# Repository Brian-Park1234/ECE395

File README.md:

Hello!

This is Brian Park (Brianp7) github for all ECE395 Files.

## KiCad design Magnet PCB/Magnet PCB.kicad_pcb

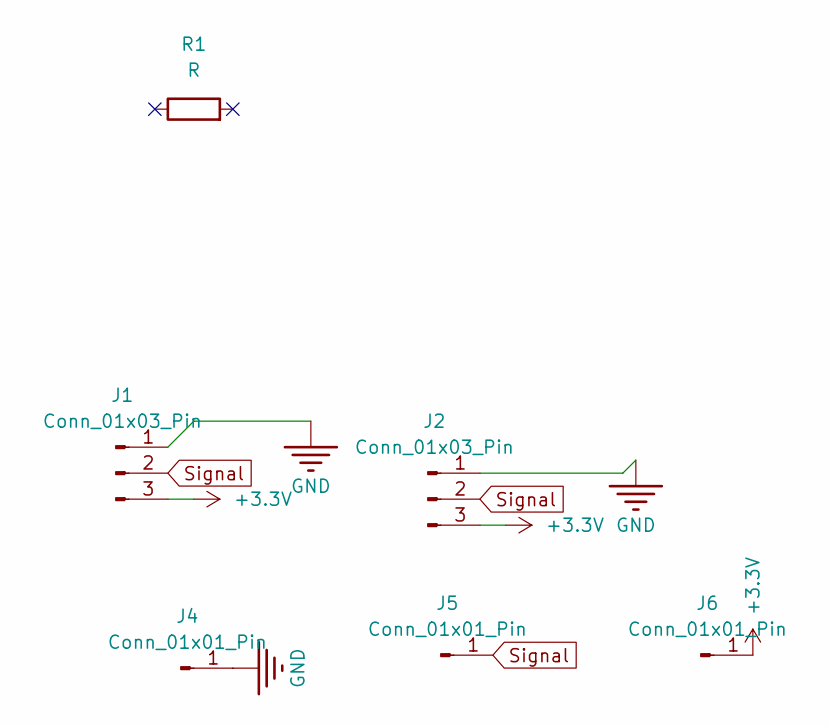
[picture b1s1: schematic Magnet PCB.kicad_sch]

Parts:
J1, J2: Conn_01x03_Pin; JST_SH_SM03B-SRSS-TB_1x03-1MP_P1.00mm_Horizontal
J4, J5, J6: Conn_01x01_Pin; CONN_0900-2-15-20-75-14-11-0_MIM
R1: R; R_0815_2038Metric

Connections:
+3.3V: J1.3, J2.3, J6.1
GND: J1.1, J2.1, J4.1
Signal: J1.2, J2.2, J5.1

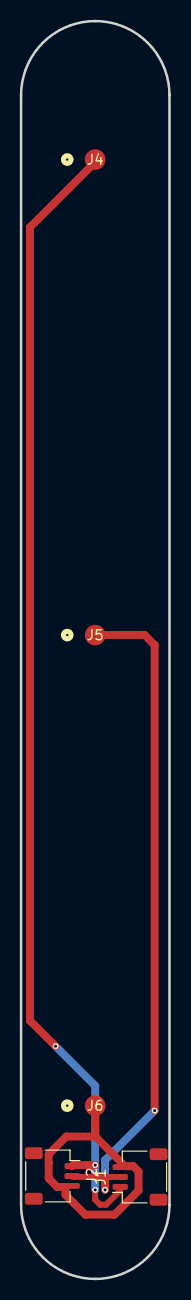
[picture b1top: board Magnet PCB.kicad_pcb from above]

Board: 2 copper layers, 15.0 x 127.0 mm, 6 parts (1 on the bottom side), 3 nets.

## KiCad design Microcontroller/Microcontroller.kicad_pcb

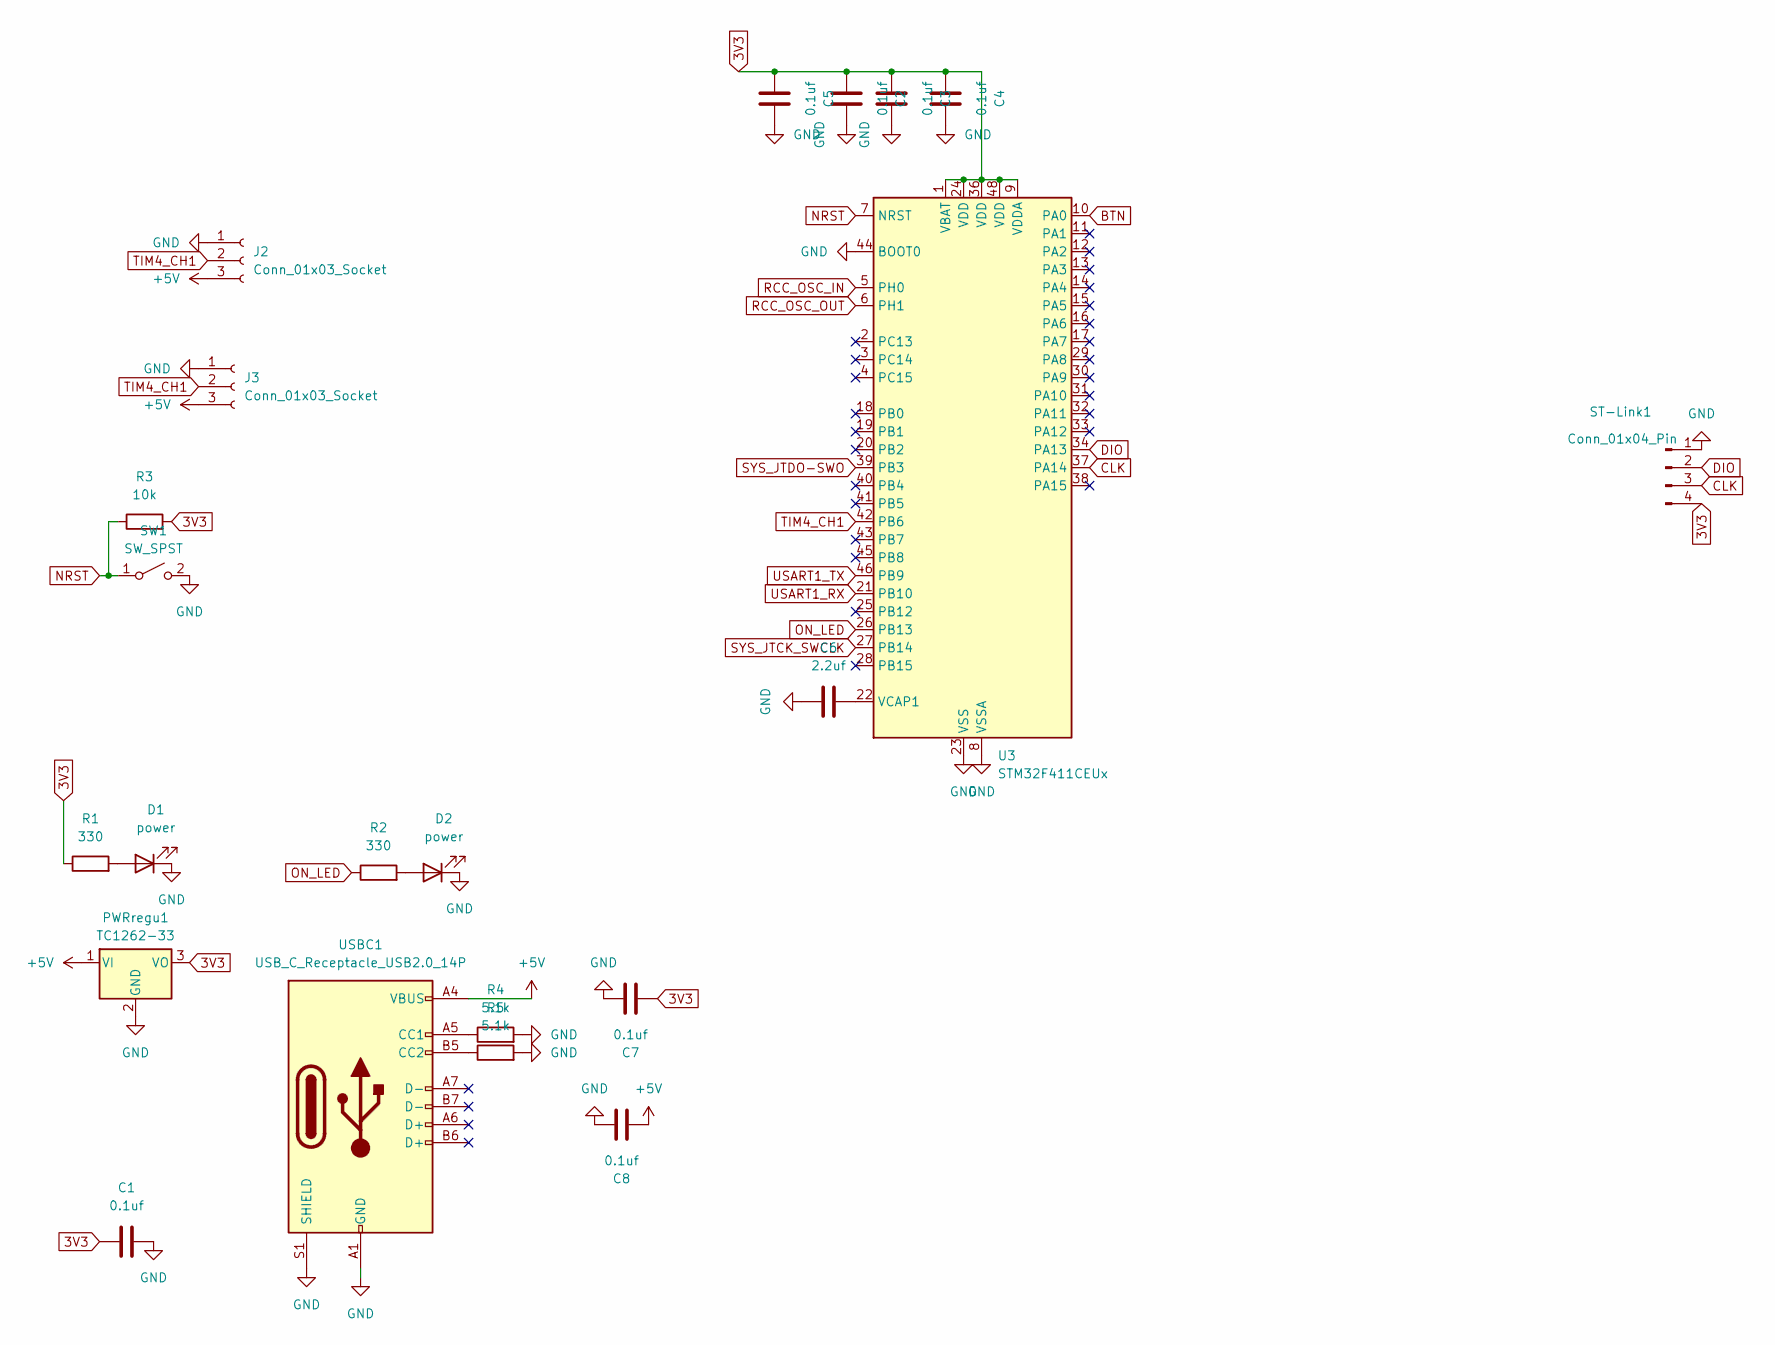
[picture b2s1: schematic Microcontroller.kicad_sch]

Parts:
C1, C2, C3, C4, C5, C7, C8: 0.1uf; C_0805_2012Metric_Pad1.18x1.45mm_HandSolder
C6: 2.2uf; C_0805_2012Metric_Pad1.18x1.45mm_HandSolder
D1, D2: power; D_0805_2012Metric
J2, J3: Conn_01x03_Socket; JST_SH_SM03B-SRSS-TB_1x03-1MP_P1.00mm_Horizontal
PWRregu1: TC1262-33; SOT-223-3_TabPin2
R1, R2: 330; R_0805_2012Metric
R3: 10k; R_0805_2012Metric
R4, R5: 5.1k; R_0805_2012Metric
ST-Link1: Conn_01x04_Pin; PinHeader_1x04_P2.54mm_Vertical
SW1: SW_SPST; SW_PUSH_6mm
U3: STM32F411CEUx; QFN-48-1EP_7x7mm_P0.5mm_EP5.6x5.6mm
USBC1: USB_C_Receptacle_USB2.0_14P; USB_C_Receptacle_GCT_USB4085

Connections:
3V3: C1.1, C2.1, C3.1, C4.1, C5.1, C7.1, PWRregu1.3 (VO), R1.1, R3.2, ST-Link1.4, U3.1 (VBAT), U3.9 (VDDA), U3.24 (VDD), U3.36 (VDD), U3.48 (VDD)
+5V: C8.1, J2.3, J3.3, PWRregu1.1 (VI), USBC1.A4 (VBUS), USBC1.A9 (VBUS), USBC1.B4 (VBUS), USBC1.B9 (VBUS)
BTN: U3.10 (PA0)
CLK: ST-Link1.3, U3.37 (PA14)
DIO: ST-Link1.2, U3.34 (PA13)
GND: C1.2, C2.2, C3.2, C4.2, C5.2, C6.2, C7.2, C8.2, D1.1 (K), D2.1 (K), J2.1, J3.1, PWRregu1.2 (GND), R4.2, R5.2, ST-Link1.1, SW1.2 (B), U3.8 (VSSA), U3.23 (VSS), U3.35 (VSS), U3.44 (BOOT0), U3.47 (VSS), U3.49 (VSS), USBC1.A1 (GND), USBC1.A12 (GND), USBC1.B1 (GND), USBC1.B12 (GND), USBC1.S1 (SHIELD); also elsewhere on the board
NRST: R3.1, SW1.1 (A), U3.7 (NRST)
unnamed: D1.2 (A), R1.2
unnamed: D2.2 (A), R2.2
unnamed: C6.1, U3.22 (VCAP1)
unnamed 10: R4.1, USBC1.A5 (CC1); also elsewhere on the board
unnamed: R5.1, USBC1.B5 (CC2)
ON_LED: R2.1, U3.26 (PB13)
RCC_OSC_IN: U3.5 (PH0)
RCC_OSC_OUT: U3.6 (PH1)
SYS_JTCK_SWCLK: U3.27 (PB14)
SYS_JTDO-SWO: U3.39 (PB3)
TIM4_CH1: J2.2, J3.2, U3.42 (PB6)
USART1_RX: U3.21 (PB10)
USART1_TX: U3.46 (PB9)

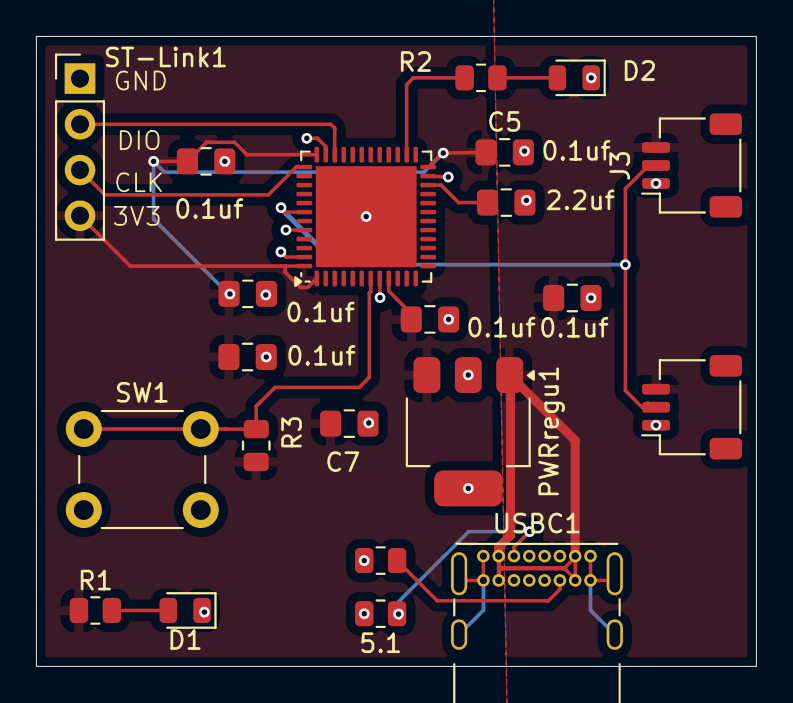
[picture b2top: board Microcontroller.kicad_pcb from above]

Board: 2 copper layers, 40.0 x 35.0 mm, 22 parts (0 on the bottom side), 13 nets.

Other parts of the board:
5.1: 5.1k; R_0805_2012Metric

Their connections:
GND: 5.1.2; also elsewhere on the board
unnamed 10: 5.1.1; also elsewhere on the board

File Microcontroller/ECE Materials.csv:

Reference,Value,Datasheet,Footprint,Qty,DNP
"C1,C2,C3,C4,C5,C6,C7,C8",0.1uf,~,Capacitor_SMD:C_0805_2012Metric_Pad1.18x1.45mm_HandSolder,8,
"D1,D2",power,~,Diode_SMD:D_0805_2012Metric,2,
"J2,J3",Conn_01x03_Socket,~,Connector_JST:JST_SH_SM03B-SRSS-TB_1x03-1MP_P1.00mm_Horizontal,2,
PWRregu1,TC1262-33,http://ww1.microchip.com/downloads/en/DeviceDoc/21373C.pdf,Package_TO_SOT_SMD:SOT-223-3_TabPin2,1,
"R1,R2",330,~,Resistor_SMD:R_0805_2012Metric,2,
R3,10k,~,Resistor_SMD:R_0805_2012Metric,1,
ST-Link1,Conn_01x04_Pin,~,Connector_PinHeader_2.54mm:PinHeader_1x04_P2.54mm_Vertical,1,
SW1,SW_SPST,~,Button_Switch_THT:SW_PUSH_6mm,1,
U3,STM32F411CEUx,https://www.st.com/resource/en/datasheet/stm32f411ce.pdf,Package_DFN_QFN:QFN-48-1EP_7x7mm_P0.5mm_EP5.6x5.6mm,1,
USBC1,USB_C_Receptacle_USB2.0_14P,https://www.usb.org/sites/default/files/documents/usb_type-c.zip,Connector_USB:USB_C_Receptacle_GCT_USB4085,1,

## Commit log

2025-12-10 Add files via upload
    Added MCU PCB
